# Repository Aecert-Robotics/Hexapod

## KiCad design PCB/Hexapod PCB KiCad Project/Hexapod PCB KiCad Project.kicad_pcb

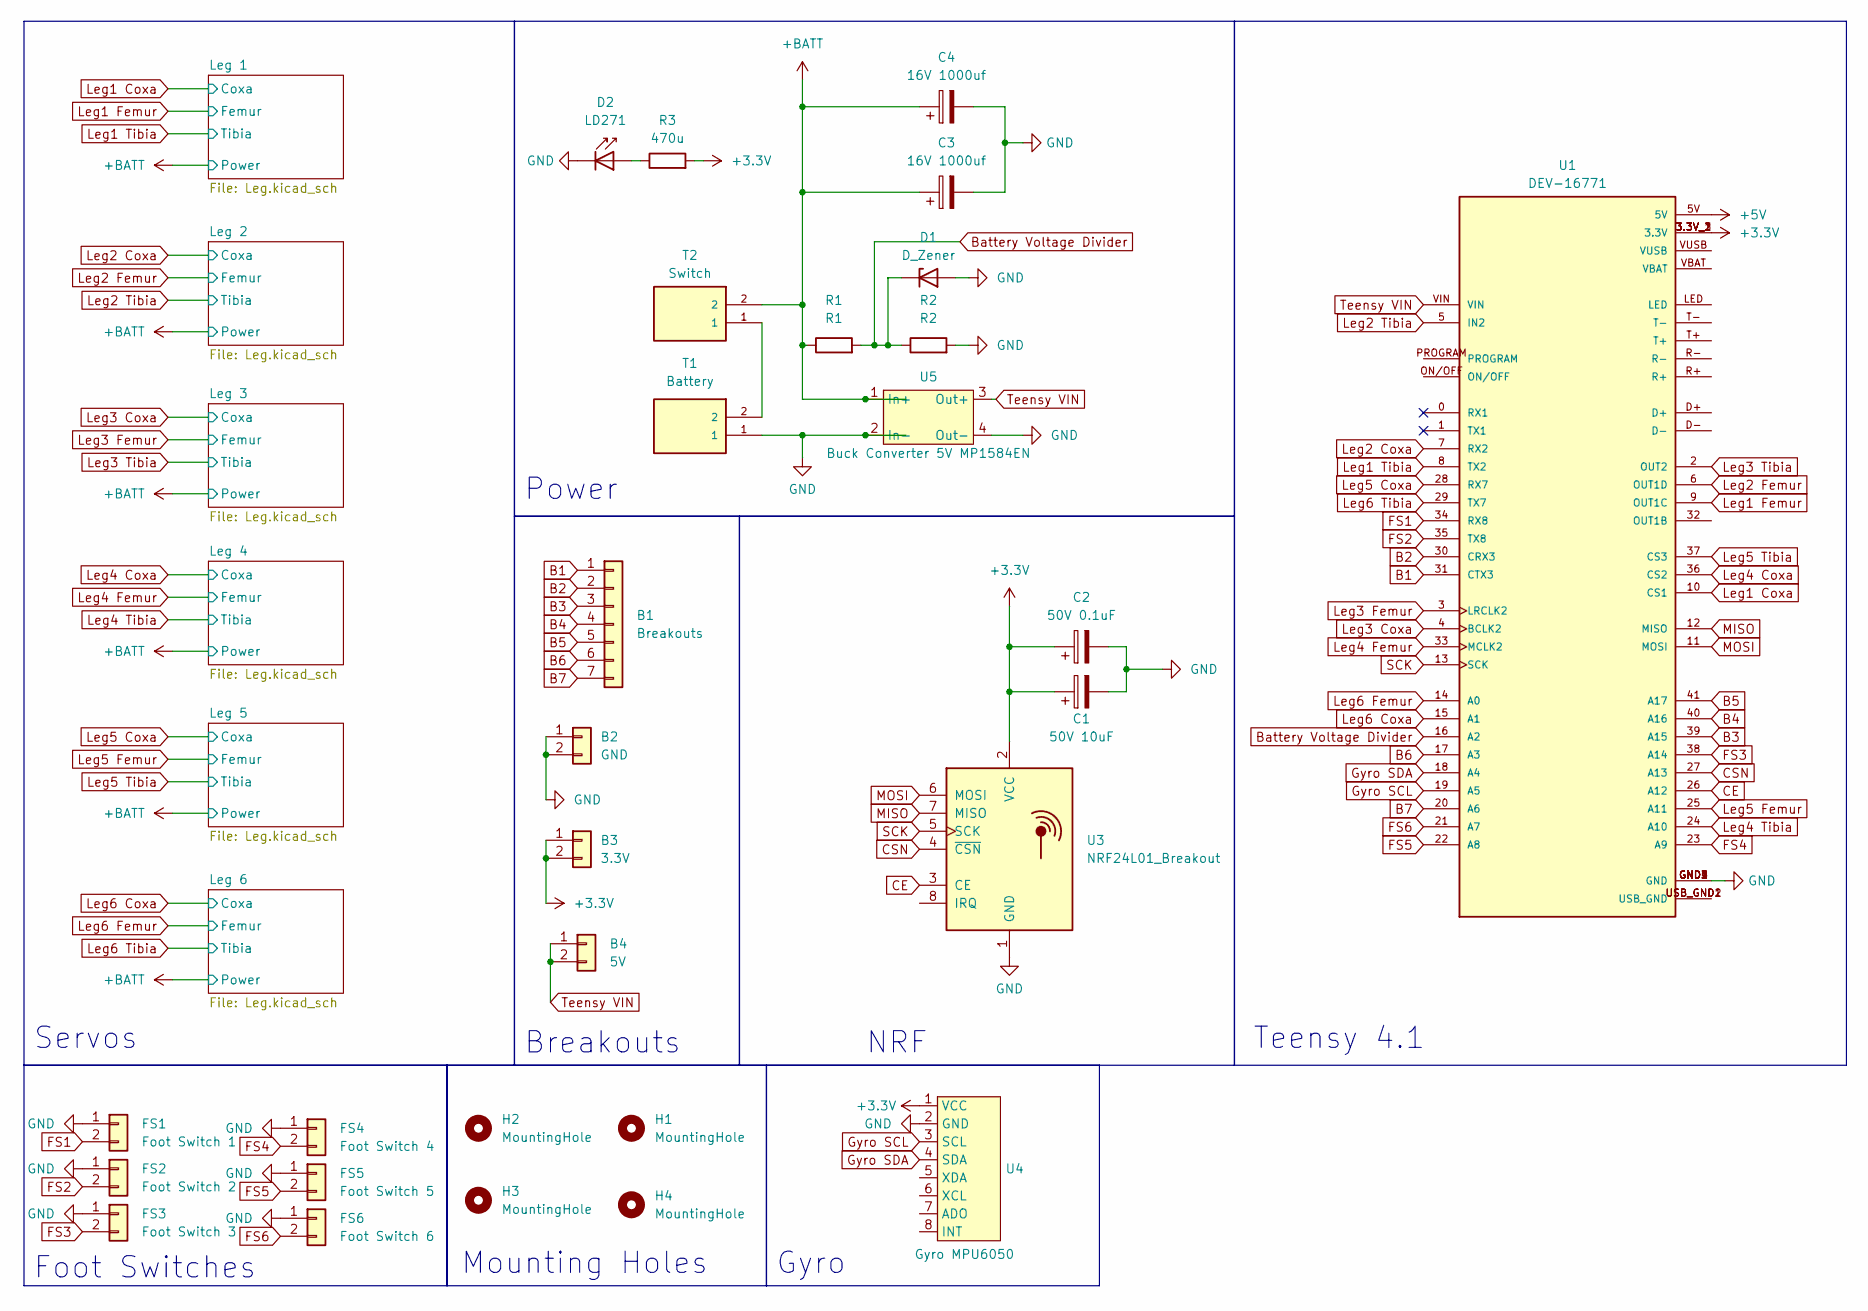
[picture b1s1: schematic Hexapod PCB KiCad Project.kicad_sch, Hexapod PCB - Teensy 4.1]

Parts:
B1: Breakouts; PinSocket_1x07_P2.54mm_Vertical
B2: GND; PinSocket_1x02_P2.54mm_Vertical
B3: 3.3V; PinSocket_1x02_P2.54mm_Vertical
B4: 5V; PinSocket_1x02_P2.54mm_Vertical
C1: 50V 10uF; CP_Radial_D5.0mm_P2.00mm
C2: 50V 0.1uF; CP_Radial_D4.0mm_P2.00mm
C3, C4: 16V 1000uf; CP_Radial_D10.0mm_P5.00mm
D1: D_Zener; D_T-1_P5.08mm_Horizontal
D2: LD271; LED_D5.0mm_IRGrey
FS1: Foot Switch 1; PinHeader_1x02_P2.54mm_Vertical
FS2: Foot Switch 2; PinHeader_1x02_P2.54mm_Vertical
FS3: Foot Switch 3; PinHeader_1x02_P2.54mm_Vertical
FS4: Foot Switch 4; PinHeader_1x02_P2.54mm_Vertical
FS5: Foot Switch 5; PinHeader_1x02_P2.54mm_Vertical
FS6: Foot Switch 6; PinHeader_1x02_P2.54mm_Vertical
H1, H2, H3, H4: MountingHole; MountingHole_3.2mm_M3
R1: R1; R_Axial_DIN0207_L6.3mm_D2.5mm_P7.62mm_Horizontal
R2: R2; R_Axial_DIN0207_L6.3mm_D2.5mm_P7.62mm_Horizontal
R3: 470u; R_Axial_DIN0207_L6.3mm_D2.5mm_P7.62mm_Horizontal
T1: Battery; CUI_TB005-762-02BE
T2: Switch; CUI_TB005-762-02BE
U1: DEV-16771; MODULE_DEV-16771; PARTREV 4.1
U3: NRF24L01_Breakout; nRF24L01_Breakout
U4: Gyro MPU6050; MPU6050 THT
U5: Buck Converter 5V MP1584EN

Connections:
+3.3V: B3.1, B3.2, C1.1, C2.1, R3.2, U1.3.3V_1 (3.3V), U1.3.3V_2 (3.3V), U1.3.3V_3 (3.3V), U3.2 (VCC), U4.1 (VCC)
+5V: U1.5V
+BATT: C3.1, C4.1, R1.1, T2.2, U5.1 (In+); also elsewhere on the board
B1: B1.1, U1.31 (CTX3)
B2: B1.2, U1.30 (CRX3)
B3: B1.3, U1.39 (A15)
B4: B1.4, U1.40 (A16)
B5: B1.5, U1.41 (A17)
B6: B1.6, U1.17 (A3)
B7: B1.7, U1.20 (A6)
Battery Voltage Divider: D1.1 (K), R1.2, R2.1, U1.16 (A2)
CE: U1.26 (A12), U3.3 (CE)
CSN: U1.27 (A13), U3.4 (~CSN)
FS1: FS1.2, U1.34 (RX8)
FS2: FS2.2, U1.35 (TX8)
FS3: FS3.2, U1.38 (A14)
FS4: FS4.2, U1.23 (A9)
FS5: FS5.2, U1.22 (A8)
FS6: FS6.2, U1.21 (A7)
GND: B2.1, B2.2, C1.2, C2.2, C3.2, C4.2, D1.2 (A), D2.1 (K), FS1.1, FS2.1, FS3.1, FS4.1, FS5.1, FS6.1, R2.2, T1.1, U1.GND1 (GND), U1.GND2 (GND), U1.GND3 (GND), U1.GND4 (GND), U1.GND5 (GND), U3.1 (GND), U4.2 (GND), U5.2 (In-), U5.4 (Out-); also elsewhere on the board
Gyro SCL: U1.19 (A5), U4.3 (SCL)
Gyro SDA: U1.18 (A4), U4.4 (SDA)
Leg1 Coxa: U1.10 (CS1); also elsewhere on the board
Leg1 Femur: U1.9 (OUT1C); also elsewhere on the board
Leg1 Tibia: U1.8 (TX2); also elsewhere on the board
Leg2 Coxa: U1.7 (RX2); also elsewhere on the board
Leg2 Femur: U1.6 (OUT1D); also elsewhere on the board
Leg2 Tibia: U1.5 (IN2); also elsewhere on the board
Leg3 Coxa: U1.4 (BCLK2); also elsewhere on the board
Leg3 Femur: U1.3 (LRCLK2); also elsewhere on the board
Leg3 Tibia: U1.2 (OUT2); also elsewhere on the board
Leg4 Coxa: U1.36 (CS2); also elsewhere on the board
Leg4 Femur: U1.33 (MCLK2); also elsewhere on the board
Leg4 Tibia: U1.24 (A10); also elsewhere on the board
Leg5 Coxa: U1.28 (RX7); also elsewhere on the board
Leg5 Femur: U1.25 (A11); also elsewhere on the board
Leg5 Tibia: U1.37 (CS3); also elsewhere on the board
Leg6 Coxa: U1.15 (A1); also elsewhere on the board
Leg6 Femur: U1.14 (A0); also elsewhere on the board
Leg6 Tibia: U1.29 (TX7); also elsewhere on the board
MISO: U1.12 (MISO), U3.7 (MISO)
MOSI: U1.11 (MOSI), U3.6 (MOSI)
unnamed: D2.2 (A), R3.1
unnamed: T1.2, T2.1
unnamed: U1.USB_GND1 (USB_GND), U1.USB_GND2 (USB_GND)
SCK: U1.13 (SCK), U3.5 (SCK)
Teensy VIN: B4.1, B4.2, U1.VIN, U5.3 (Out+)

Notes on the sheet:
Foot Switches
Gyro
Teensy 4.1
Servos
Power
Mounting Holes
Breakouts
NRF

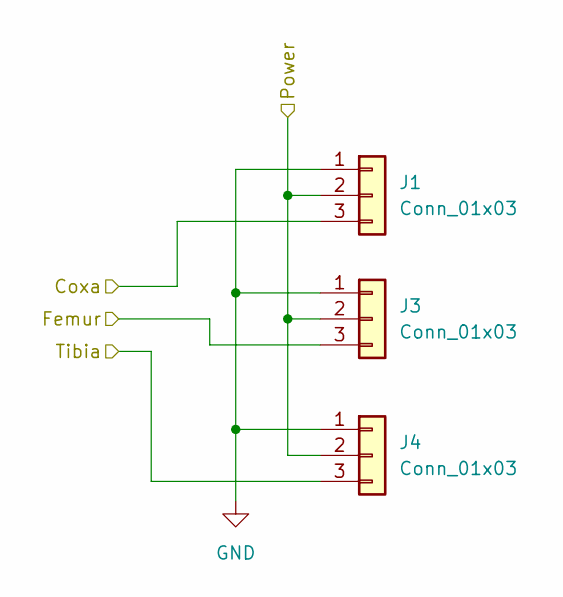
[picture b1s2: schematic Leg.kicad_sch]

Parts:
J1, J3, J4: Conn_01x03; PinHeader_1x03_P2.54mm_Vertical

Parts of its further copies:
Cox1, Cox2, Cox3, Cox4, Cox5, Cox6: Conn_01x03; PinHeader_1x03_P2.54mm_Vertical
Fem1, Fem2, Fem3, Fem4, Fem5, Fem6: Conn_01x03; PinHeader_1x03_P2.54mm_Vertical
Tib1, Tib2, Tib3, Tib4, Tib5, Tib6: Conn_01x03; PinHeader_1x03_P2.54mm_Vertical

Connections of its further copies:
+BATT: Cox1.2, Cox2.2, Cox3.2, Cox4.2, Cox5.2, Cox6.2, Fem1.2, Fem2.2, Fem3.2, Fem4.2, Fem5.2, Fem6.2, Tib1.2, Tib2.2, Tib3.2, Tib4.2, Tib5.2, Tib6.2; also elsewhere on the board
GND: Cox1.1, Cox2.1, Cox3.1, Cox4.1, Cox5.1, Cox6.1, Fem1.1, Fem2.1, Fem3.1, Fem4.1, Fem5.1, Fem6.1, Tib1.1, Tib2.1, Tib3.1, Tib4.1, Tib5.1, Tib6.1; also elsewhere on the board
Leg1 Coxa: Cox6.3; also elsewhere on the board
Leg1 Femur: Fem6.3; also elsewhere on the board
Leg1 Tibia: Tib6.3; also elsewhere on the board
Leg2 Coxa: Cox5.3; also elsewhere on the board
Leg2 Femur: Fem5.3; also elsewhere on the board
Leg2 Tibia: Tib5.3; also elsewhere on the board
Leg3 Coxa: Cox4.3; also elsewhere on the board
Leg3 Femur: Fem4.3; also elsewhere on the board
Leg3 Tibia: Tib4.3; also elsewhere on the board
Leg4 Coxa: Cox3.3; also elsewhere on the board
Leg4 Femur: Fem3.3; also elsewhere on the board
Leg4 Tibia: Tib3.3; also elsewhere on the board
Leg5 Coxa: Cox2.3; also elsewhere on the board
Leg5 Femur: Fem2.3; also elsewhere on the board
Leg5 Tibia: Tib2.3; also elsewhere on the board
Leg6 Coxa: Cox1.3; also elsewhere on the board
Leg6 Femur: Fem1.3; also elsewhere on the board
Leg6 Tibia: Tib1.3; also elsewhere on the board

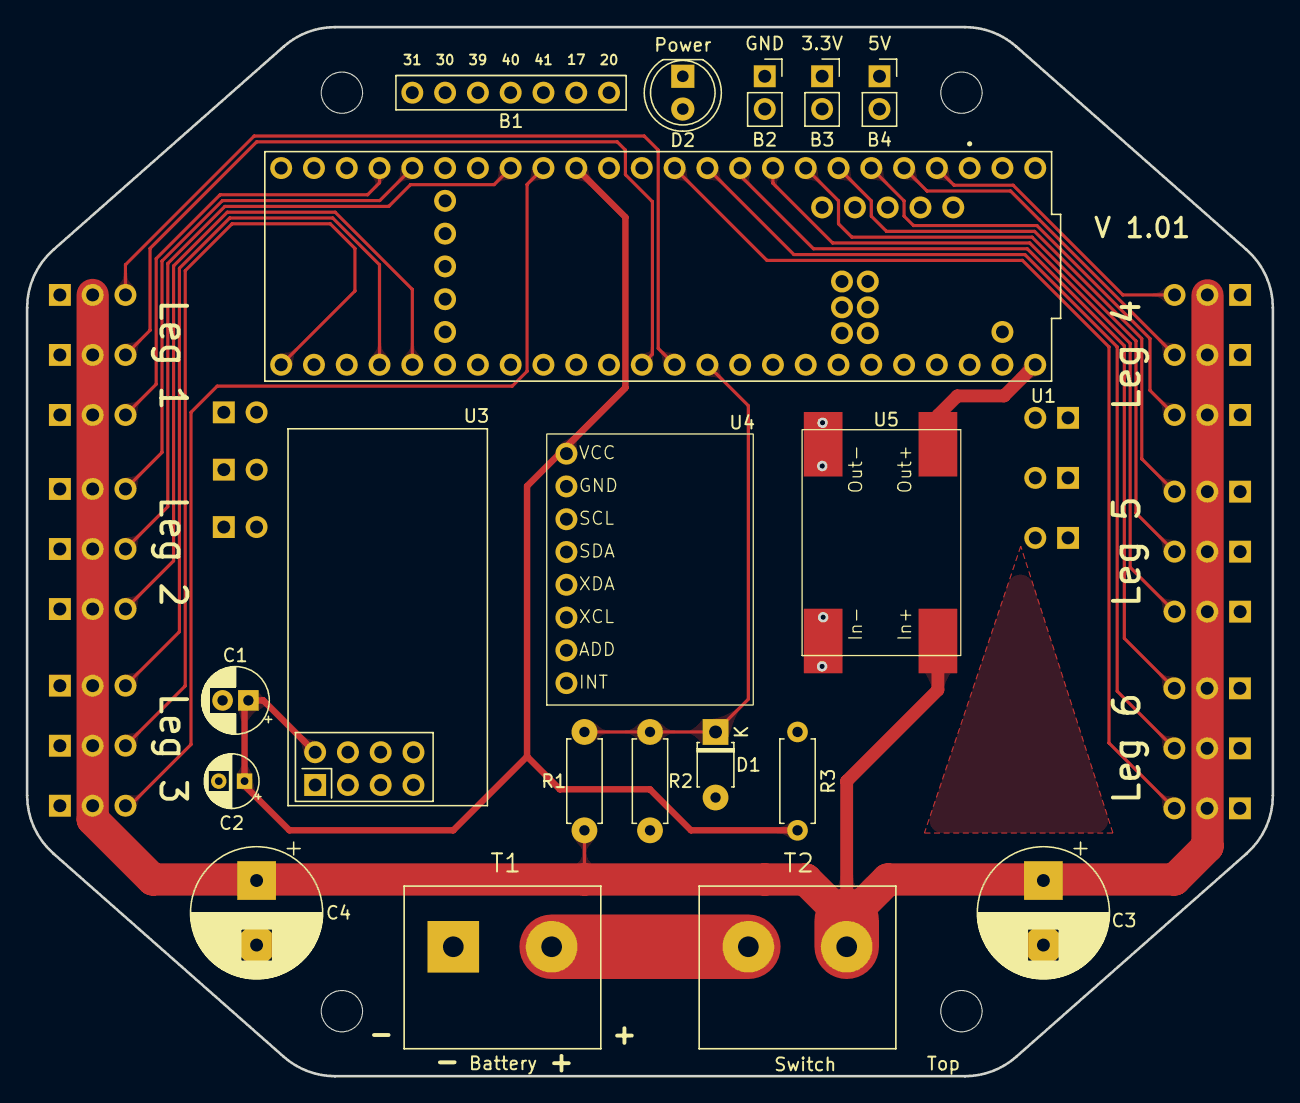
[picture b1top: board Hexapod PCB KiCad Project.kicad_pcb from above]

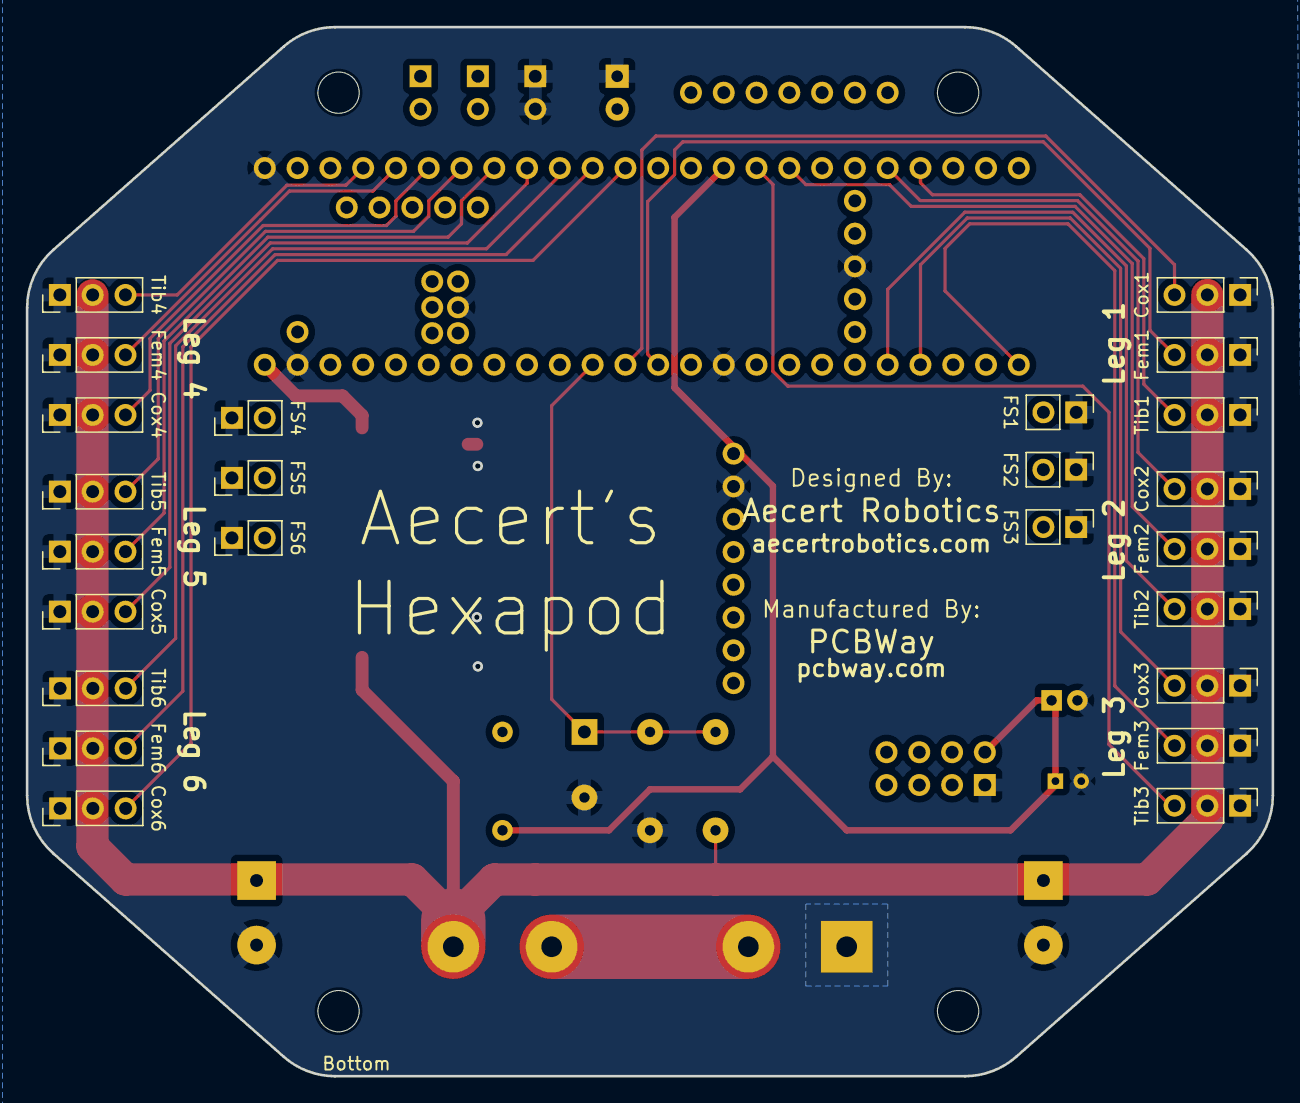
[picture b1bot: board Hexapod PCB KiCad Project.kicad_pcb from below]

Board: 4 copper layers, 96.5 x 81.3 mm, 47 parts (24 on the bottom side), 46 nets.

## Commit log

2025-02-16 created kicad project, imported teensy 4.1 symbol, footprint, and 3d model.
2025-02-17 pcb updates
2025-02-21 pcb 3d models
2025-02-21 sheet data
2025-02-22 traces
2025-02-23 breakout updates
2025-03-02 PCB V1 Finished
2025-03-03 battery clip & screen spacers
2025-03-04 chamfers and holes
2025-03-04 fixes
2025-03-04 increased height for 40mm screw
2025-03-05 stl updates
2025-03-05 power switch holder
2025-03-08 femur
2025-03-11 spring and foot stuff
2025-03-18 stls
2025-03-18 fixed power switch
2025-03-19 Battery Clip update + Frame bottom
2025-03-22 pcb v1.01
2025-03-26 updated stls
2025-03-26 assembled pics
2025-03-26 pcb fixes
2025-03-26 foot shaft length fix
2025-03-27 smaller leg
2025-03-29 Stand
2025-03-29 pcb tests
2025-03-29 new code project
2025-03-30 sleep state WORKING
2025-04-02 States
2025-04-02 everything
2025-04-05 loop time + smooth movement + refactors
2025-04-05 Walking State implemented and working
2025-04-05 Calibration state working
2025-04-06 walking state fixed
2025-04-06 Added an "exit" function
    Added an "exit" function that runs after a state is exited, but before the new states "init" function runs.
    currently its only used to run the save calibration offsets function once the calibration state is exited.
2025-04-09 servo cases
2025-04-09 Added assemebly stl
2025-04-09 Smoother movement
2025-04-21 major refactors to walking related things
2025-04-21 Fixed Standing State
2025-04-21 Standing state now adjusts one leg at a time
    The 3 legs at a time method that was previously used only worked properly 100% of the time with Tri gait. 1 leg at a time works with every gait.
2025-04-21 hop gait adjusted
2025-04-21 refactor
2025-04-21 gyro state
2025-05-24 gyro
